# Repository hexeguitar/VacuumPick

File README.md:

# VacuumPick
### DIY vacuum pick up project for hand SMT assembly. 
The hardware is based around an inexpensive air pump, 3 valves and a controller board utilizing the ATTINY806 microcontroller.  
Firmware is available as PlatformIO project (sources) and a precompiled hex file.  
The enclosure and the handle was reused from a damaged Ayoue932 vacuum pick up.

![alt text][pic8]  

--- 
### Operation
* vacuum activated using a touch button on the handle or a footswitch
*  Button 1: Vacuum mode
*  Button 2: Clean/air blow mode for cleaning the nozzle
*  Button 3: pump always on mode
*  0-100% pump speed control using a potentiometer

![alt text][pic11]
![alt text][pic9]
![alt text][pic10]
   ___   
### Electronics  
* ATTINY806 MCU  
* 3 x open drain MOSFET outputs for valve controls
* 3 x illuminated button inputs
* Footswitch or handle button input (incl. 5V power for touch sensors)
* Pot input as motor speed control
* UART TX/RX for debugging purposes
* I2C header for future expansion
* UPDI programmer input
* 12V DC 1A input power requirement  

Board is designed in **KiCad 6.0**, available as project and generated gerber files.   
### [Schematic]

![alt text][pic7]  
![alt text][pic2]  

   ---   
### Mechanical design  
Design is done using FreeCAD:  

![alt text][pic3]      
![alt text][pic4]
![alt text][pic6] 

The main parts are:  
* Base plate used to mount the pump holder and the rest of the assembly (see [MountingPlates])
* Top plate used to mount the valves
* 2 part 3D printed pump holder (step files are available)
* Valve holder - 3D printed part
* Various hardware: M3 standoffs, screws, locknuts, etc.  
 
---  
### System  

![alt text][pic12] 

---  
### Handle  

![alt text][pic14]

Pump can be controlled using either a footswitch or a button installed directly on the handle. The latter is my preferred method which i'm quite used to. I decided to install a capacitive touch button near the hole on the handle achieve two things:
* a slight move of the finger covering the hole enables the pump and increases the suction force
* to release the part all i need to do is to move the finger out of hole, this stops the pump and releases the part.  
  
The touch sensor is made of a piece of thin copper clad and uses the TTP223D-MA6 capacitive touch button IC. There are a few variants of the TTP223 chip, some having an option for open drain or push-pull output. The one i have has one control pin only (momentary/toggle operation) and an open drain output. The board is designed to work with this type of the output, so in case you are using a different model, make sure it's properly configured.  

![alt text][pic13]  

This is a small board i designed for the TTP223-MA6 chip. Important feature is the touch sensor sensitivity adjustment using a small 0 - 51pF 0603 capacitor placed in parallel with the input. Experiment with a value to get a desired button response. In my case (handle made of metal) i had to add a 47pf cap to make it work reliably. Otherwise even touching the handle would enable the pump.  

![alt text][pic15]  

Once installed everything was secured using a heat shrink tube.  

--- 
VacuumPick in action:  

----  
Copyright 2021 by Piotr Zapart  
www.hexefx.com

[pic1]: pics/vacuum3.jpg "VaccumPick"
[pic2]: pics/vpick_rnd4.jpg "VaccumPick"
[pic3]: pics/vpick_rnd1.jpg "VaccumPick"
[pic4]: pics/vpick_rnd2.jpg "VaccumPick"
[pic5]: pics/vpick_rnd3.jpg "VaccumPick"
[pic6]: pics/vpick_parts.jpg "VaccumPick"
[pic7]: pics/vpick_pcb_kicad.gif "VaccumPick"
[pic8]: pics/vpick1.jpg "VaccumPick"
[pic9]: pics/vpick2.jpg "VaccumPick"
[pic10]: pics/vpick3.jpg "VaccumPick"
[pic11]: pics/vpick4.jpg "VaccumPick"
[pic12]: Hardware/VacuumPick_system.gif "VaccumPick"
[pic13]: pics/handle1.jpg "VaccumPick-Handle"
[pic14]: pics/handle2.jpg "VaccumPick-Handle"
[pic15]: pics/handle3.jpg "VaccumPick-Handle"

[Schematic]: /Hardware/VacuumPick_schm.pdf "Schematic"
[MountingPlates]: /Hardware/VacuumPick_MountingPlates.pdf "Plates mech. drawings"

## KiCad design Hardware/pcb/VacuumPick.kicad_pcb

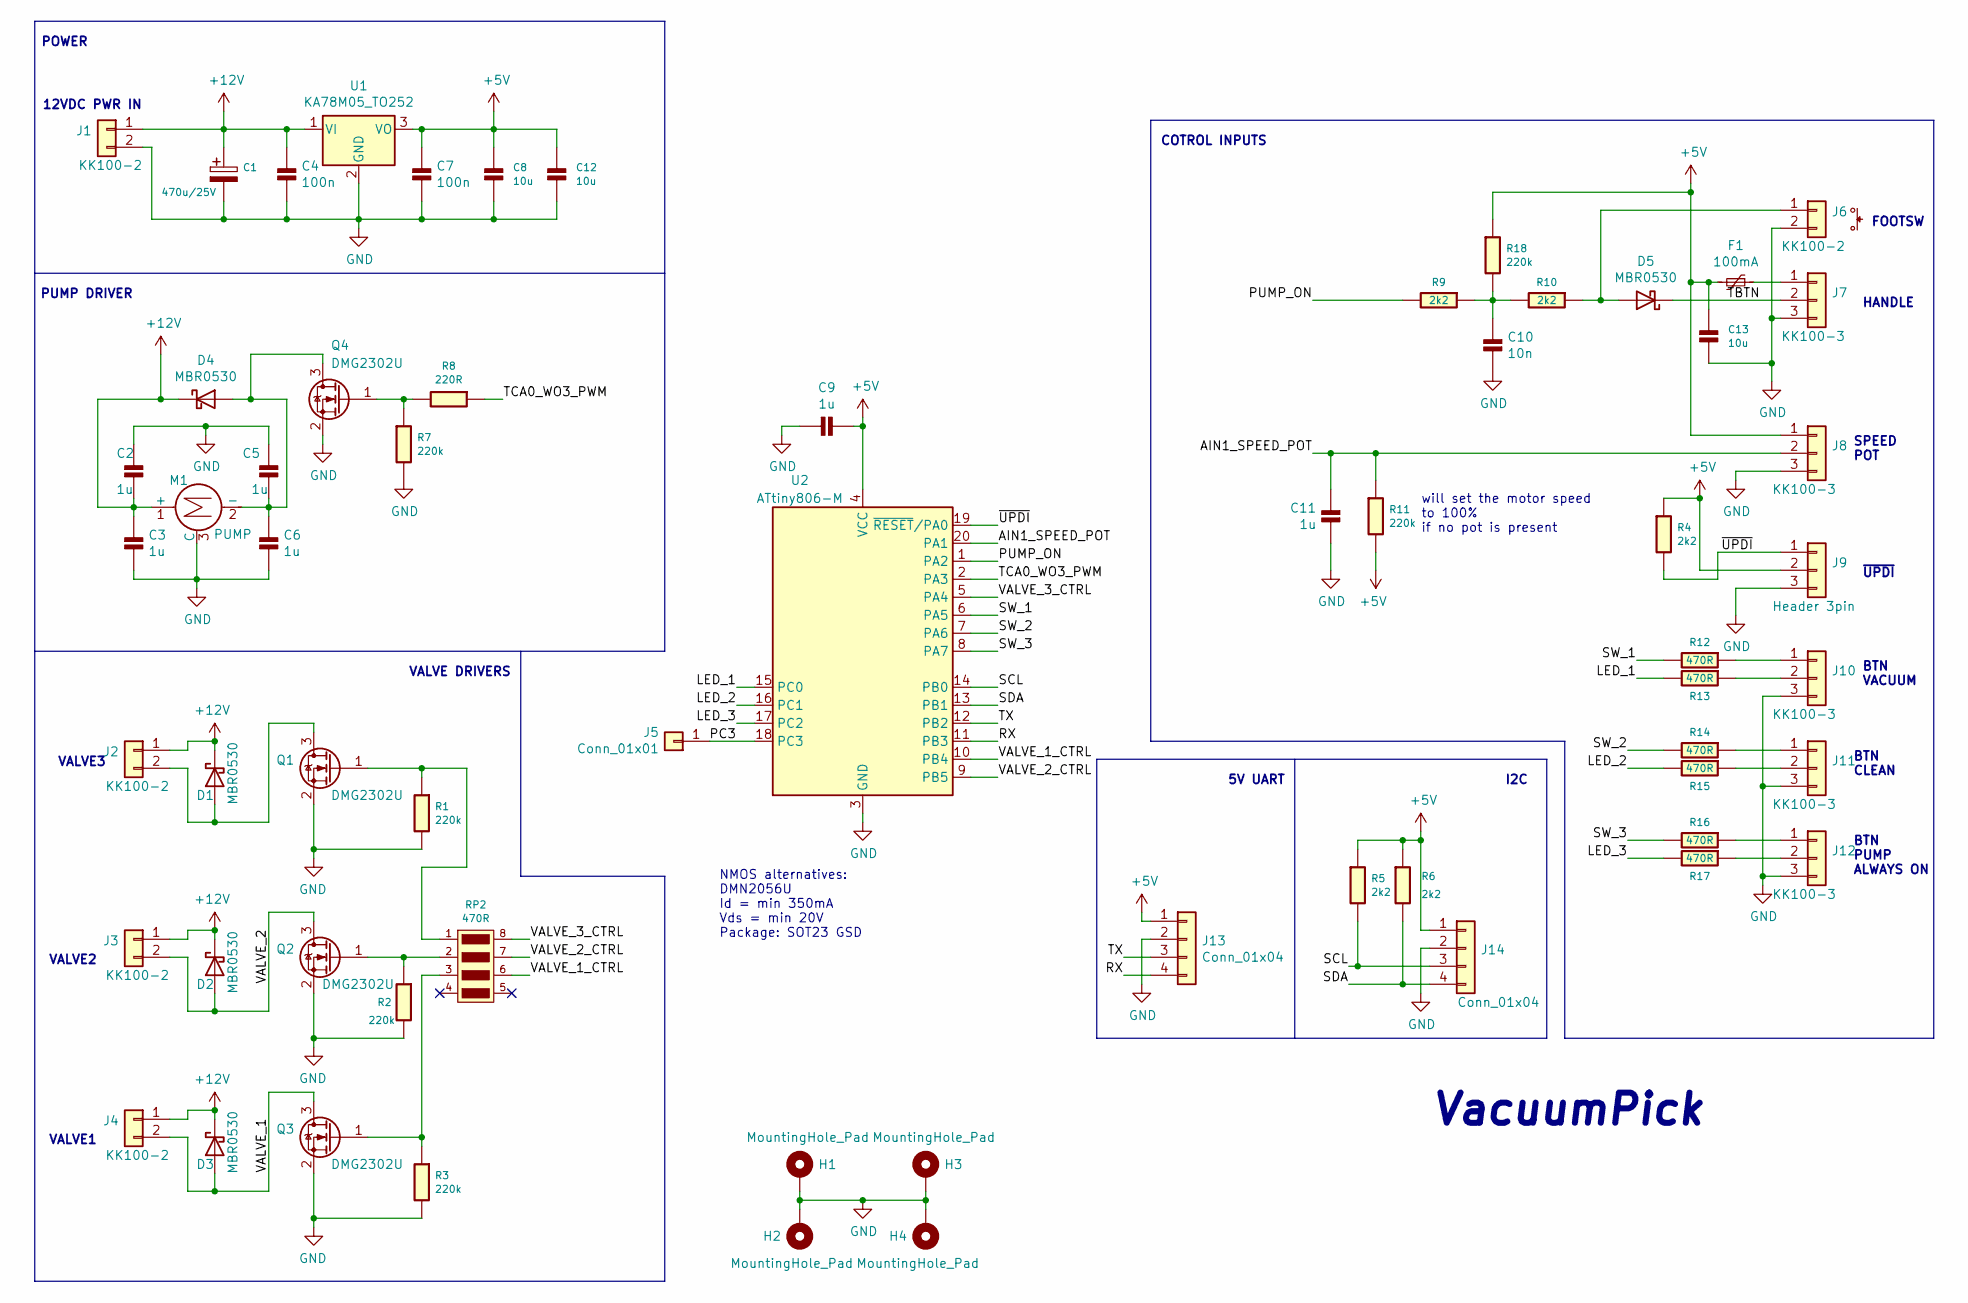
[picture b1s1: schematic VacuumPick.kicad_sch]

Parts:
C1: 470u/25V; CP_Radial_D8.0mm_P3.50mm
C2, C3, C5, C6, C9, C11: 1u; Hx_C_0805_2012Metric
C4, C7: 100n; Hx_C_0805_2012Metric
C8, C12, C13: 10u; Hx_C_0805_2012Metric
C10: 10n; Hx_C_0805_2012Metric
D1, D2, D3, D4, D5: MBR0530; D_SOD-123
F1: 100mA; Fuse_1206_3216Metric
H1: MountingHole_Pad; MountingHole_2.7mm_M2.5_DIN965_Pad
H2, H3, H4: MountingHole_Pad; MountingHole_2.7mm_M2.5_ISO7380_Pad
J1, J2, J3, J4, J6: KK100-2; 1x2_254_socket_H
J5: Conn_01x01; TestPoint_Pad_D1.5mm
J7, J8, J10, J11, J12: KK100-3; 1x3_254_socket_H
J9: Header 3pin; PinHeader_1x03_P2.54mm_Vertical
J13, J14: Conn_01x04; PinHeader_1x04_P2.54mm_Vertical
M1: PUMP; VacuumPump_DC12V
Q1, Q2, Q3, Q4: DMG2302U; SOT-23
R1, R2, R3, R7, R11, R18: 220k; Hx_R_0805_2012Metric
R4, R5, R6, R9, R10: 2k2; Hx_R_0805_2012Metric
R8: 220R; Hx_R_0805_2012Metric
R12, R13, R14, R15, R16, R17: 470R; Hx_R_0805_2012Metric
RP2: 470R; R_Array_Convex_4x0603
U1: KA78M05_TO252; TO-252-2
U2: ATtiny806-M; VQFN-20-1EP_3x3mm_P0.4mm_EP1.7x1.7mm

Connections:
+5V: C7.1, C8.1, C9.1, C12.1, C13.1, F1.2, J8.1, J9.2, J13.1, J14.1, R4.1, R5.1, R6.1, R11.2, R18.1, U1.3 (VO), U2.4 (VCC)
+12V: C1.1, C2.2, C3.1, C4.1, D1.1 (K), D2.1 (K), D3.1 (K), D4.1 (K), J1.1, J2.1, J3.1, J4.1, M1.1 (+), U1.1 (VI)
/AIN1_SPEED_POT: C11.2, J8.2, R11.1, U2.20 (PA1)
/LED_1: R13.2, U2.15 (PC0)
/LED_2: R15.2, U2.16 (PC1)
/LED_3: R17.2, U2.17 (PC2)
/PC3: J5.1, U2.18 (PC3)
/PUMP_ON: R9.2, U2.1 (PA2)
/RX: J13.4, U2.11 (PB3)
/SCL: J14.3, R5.2, U2.14 (PB0)
/SDA: J14.4, R6.2, U2.13 (PB1)
/SW_1: R12.2, U2.6 (PA5)
/SW_2: R14.2, U2.7 (PA6)
/SW_3: R16.2, U2.8 (PA7)
/TBTN: D5.1 (K), J7.2
/TCA0_WO3_PWM: R8.1, U2.2 (PA3)
/TX: J13.3, U2.12 (PB2)
/VALVE_1: D3.2 (A), J4.2, Q3.3 (D)
/VALVE_1_CTRL: RP2.6 (R3), U2.10 (PB4)
/VALVE_2: D2.2 (A), J3.2, Q2.3 (D)
/VALVE_2_CTRL: RP2.7 (R2), U2.9 (PB5)
/VALVE_3_CTRL: RP2.8 (R1), U2.5 (PA4)
/~UPDI: J9.1, R4.2, U2.19 (~RESET/PA0)
GND: C1.2, C2.1, C3.2, C4.2, C5.1, C6.2, C7.2, C8.2, C9.2, C10.1, C11.1, C12.2, C13.2, H1.1, H2.1, H3.1, H4.1, J1.2, J6.2, J7.3, J8.3, J9.3, J10.3, J11.3, J12.3, J13.2, J14.2, M1.3 (C), Q1.2 (S), Q2.2 (S), Q3.2 (S), Q4.2 (S), R1.2, R2.2, R3.2, R7.2, U1.2 (GND), U2.3 (GND), U2.21 (GND)
unnamed: C5.2, C6.1, D4.2 (A), M1.2 (-), Q4.3 (D)
unnamed: C10.2, R9.1, R10.2, R18.2
unnamed: D1.2 (A), J2.2, Q1.3 (D)
unnamed: D5.2 (A), J6.1, R10.1
unnamed: F1.1, J7.1
unnamed: J10.1, R12.1
unnamed: J10.2, R13.1
unnamed: J11.1, R14.1
unnamed: J11.2, R15.1
unnamed: J12.1, R16.1
unnamed: J12.2, R17.1
unnamed: Q1.1 (G), R1.1, RP2.1
unnamed: Q2.1 (G), R2.1, RP2.2
unnamed: Q3.1 (G), R3.1, RP2.3
unnamed: Q4.1 (G), R7.1, R8.2

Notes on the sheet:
BTN VACUUM
~{UPDI}
PUMP DRIVER
5V UART
VALVE DRIVERS
BTN PUMP ALWAYS ON
FOOTSW
VALVE3
I2C
SPEED POT
NMOS alternatives: DMN2056U Id = min 350mA Vds = min 20V Package: SOT23 GSD
VacuumPick
VALVE2
BTN CLEAN
12VDC PWR IN
COTROL INPUTS
VALVE1
POWER
will set the motor speed to 100% if no pot is present
HANDLE

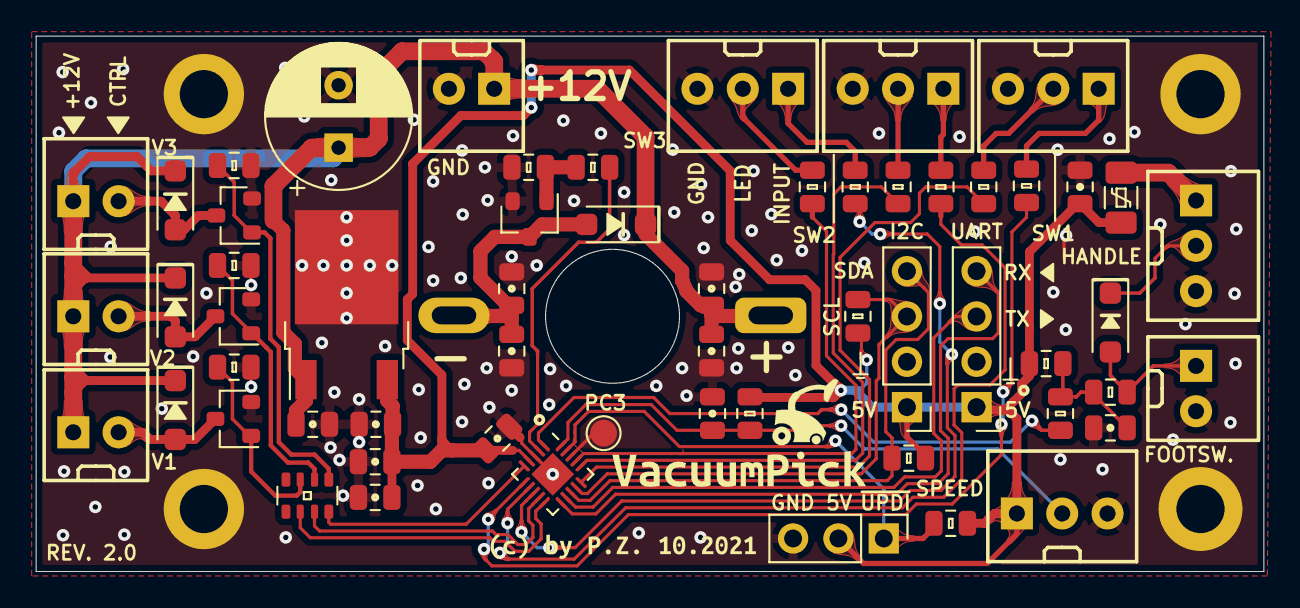
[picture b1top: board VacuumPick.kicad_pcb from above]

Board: 2 copper layers, 68.8 x 30.0 mm, 65 parts (0 on the bottom side), 39 nets.

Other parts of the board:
kibuzzard-61600490, kibuzzard-61600814: G***; label

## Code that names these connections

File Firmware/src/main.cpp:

/*
 * Copyright (c) 2021 by Piotr Zapart / www.hexefx.com
 *
 * All rights reserved.
 *
 * Redistribution and use in source and binary forms, with or without modification, 
 * are permitted provided that the following conditions are met:
 *
 * Redistributions of source code must retain the above copyright notice, this list 
 * of conditions and the following disclaimer.
 * 
 * Redistributions in binary form must reproduce the above copyright notice, this 
 * list of conditions and the following disclaimer in the documentation and/or other
 * materials provided with the distribution.
 *  
 * Neither the name of the Piotr Zapart or HEXE FX nor the names of its 
 * contributors may be used to endorse or promote products derived from this software 
 * without specific prior written permission.
 * 
 * THIS SOFTWARE IS PROVIDED BY THE COPYRIGHT HOLDERS AND CONTRIBUTORS "AS IS" 
 * AND ANY EXPRESS OR IMPLIED WARRANTIES, INCLUDING, BUT NOT LIMITED TO, THE IMPLIED 
 * WARRANTIES OF MERCHANTABILITY AND FITNESS FOR A PARTICULAR PURPOSE ARE DISCLAIMED. 
 * IN NO EVENT SHALL THE COPYRIGHT HOLDER OR CONTRIBUTORS BE LIABLE FOR ANY DIRECT, 
 * INDIRECT, INCIDENTAL, SPECIAL, EXEMPLARY, OR CONSEQUENTIAL DAMAGES (INCLUDING, BUT 
 * NOT LIMITED TO, PROCUREMENT OF SUBSTITUTE GOODS OR SERVICES; LOSS OF USE, DATA, 
 * OR PROFITS; OR BUSINESS INTERRUPTION) HOWEVER CAUSED AND ON ANY THEORY OF LIABILITY, 
 * WHETHER IN CONTRACT, STRICT LIABILITY, OR TORT (INCLUDING NEGLIGENCE OR OTHERWISE) 
 * ARISING IN ANY WAY OUT OF THE USE OF THIS SOFTWARE, EVEN IF ADVISED OF THE POSSIBILITY
 * OF SUCH DAMAGE.
 * 
 */
#include <Arduino.h>
#include "button.h"
#include "Wire.h"
#include "pump.h"
#include "valve.h"

// pin definiions 
#define POT_PIN     PIN_PA1

#define V1_PIN      PIN_PB4
#define V2_PIN      PIN_PB5
#define V3_PIN      PIN_PA4

#define LED1_PIN    PIN_PC0
#define LED2_PIN    PIN_PC1
#define LED3_PIN    PIN_PC2

#define PUMP_PIN    PIN_PA3

uint8_t speed = 0, speed_old = 0;

ValveSystem valves(V1_PIN, V2_PIN, V3_PIN);
Pump pump(PUMP_PIN);

void setup()
{
    //Serial.begin(115200);
    //Serial.println(F("VacuumPick"));
    pump.init();
    pinMode(LED1_PIN, OUTPUT); digitalWrite(LED1_PIN, HIGH);
    pinMode(LED2_PIN, OUTPUT); digitalWrite(LED2_PIN, LOW);
    pinMode(LED3_PIN, OUTPUT); digitalWrite(LED3_PIN, LOW);

    btn_init();
    analogReadResolution(8);
}

void loop()
{
    speed = analogRead(POT_PIN);
    if (speed != speed_old)
    {
        pump.setSpeed(speed);
        speed_old = speed;
    }

    if (btn_get_press(1<<BTN1))
    {
        valves.set(VALVE_MODE_VACUUM);
        digitalWriteFast(LED1_PIN, HIGH);
        digitalWriteFast(LED2_PIN, LOW);
    }
    if (btn_get_press(1<<BTN2))
    {
        valves.set(VALVE_MODE_BLOW);
        digitalWriteFast(LED1_PIN, LOW);
        digitalWriteFast(LED2_PIN, HIGH);
    }
    if (btn_get_press(1<<BTN3))
    {
        bool result = pump.toogleAlwaysOn();
        digitalWrite(LED3_PIN, result);
    }
    if (btn_get_press(1<<PUMP_EN))
    {
        pump.on();
    }
    if (btn_get_release(1<<PUMP_EN))
    {
        pump.off();
    }
    if (btn_get_long(1<<PUMP_EN))
    {
        Serial.println(F("Pump LONG"));
    }

    pump.update();
}

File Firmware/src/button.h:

/*
 * Copyright (c) 2021 by Piotr Zapart / www.hexefx.com
 *
 * All rights reserved.
 *
 * Redistribution and use in source and binary forms, with or without modification, 
 * are permitted provided that the following conditions are met:
 *
 * Redistributions of source code must retain the above copyright notice, this list 
 * of conditions and the following disclaimer.
 * 
 * Redistributions in binary form must reproduce the above copyright notice, this 
 * list of conditions and the following disclaimer in the documentation and/or other
 * materials provided with the distribution.
 *  
 * Neither the name of the Piotr Zapart or HEXE FX nor the names of its 
 * contributors may be used to endorse or promote products derived from this software 
 * without specific prior written permission.
 * 
 * THIS SOFTWARE IS PROVIDED BY THE COPYRIGHT HOLDERS AND CONTRIBUTORS "AS IS" 
 * AND ANY EXPRESS OR IMPLIED WARRANTIES, INCLUDING, BUT NOT LIMITED TO, THE IMPLIED 
 * WARRANTIES OF MERCHANTABILITY AND FITNESS FOR A PARTICULAR PURPOSE ARE DISCLAIMED. 
 * IN NO EVENT SHALL THE COPYRIGHT HOLDER OR CONTRIBUTORS BE LIABLE FOR ANY DIRECT, 
 * INDIRECT, INCIDENTAL, SPECIAL, EXEMPLARY, OR CONSEQUENTIAL DAMAGES (INCLUDING, BUT 
 * NOT LIMITED TO, PROCUREMENT OF SUBSTITUTE GOODS OR SERVICES; LOSS OF USE, DATA, 
 * OR PROFITS; OR BUSINESS INTERRUPTION) HOWEVER CAUSED AND ON ANY THEORY OF LIABILITY, 
 * WHETHER IN CONTRACT, STRICT LIABILITY, OR TORT (INCLUDING NEGLIGENCE OR OTHERWISE) 
 * ARISING IN ANY WAY OUT OF THE USE OF THIS SOFTWARE, EVEN IF ADVISED OF THE POSSIBILITY
 * OF SUCH DAMAGE.
 * 
 */
#ifndef _BUTTON_H
#define _BUTTON_H

#include <Arduino.h>

#define BTN1        5
#define BTN2        6
#define BTN3        7
#define PUMP_EN     2
#define BTN1_PIN    PIN_PA5
#define BTN2_PIN    PIN_PA6
#define BTN3_PIN    PIN_PA7
#define PUMP_EN_PIN PIN_PA2

#define BTN_MASK    ((1<<BTN1)|(1<<BTN2)|(1<<BTN3)|(1<<PUMP_EN))

void btn_init(void);
uint8_t btn_get_long(uint8_t btn_mask);
uint8_t btn_get_press(uint8_t btn_mask);
uint8_t btn_get_release(uint8_t btn_mask);


#endif // _BUTTON_H

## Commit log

2021-12-27 major update
2021-12-27 missing files
2021-12-28 readme update
